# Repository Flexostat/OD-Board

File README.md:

# OD-Board
This repository contains the optical density measurement PCB and firmware source
 and production files for the Flexostat and syphonstat.

### Production_files/PCB/
These are the files that get zipped and sent to the PCB fabricator.

### Production_files/firmware.hex
This is the firmware file to be loaded onto the OD board.  

### seeed_bom.csv
This is the BOM file used by Seeedstudio to assemble the PCB.  If assembled by
Seeedstudio, the light sensors still need to be added afterwards since seeed
does not stock them.

<br />This work is licensed under a <a rel="license" href="http://creativecommons.org/licenses/by/4.0/">Creative Commons Attribution 4.0 International License</a>.

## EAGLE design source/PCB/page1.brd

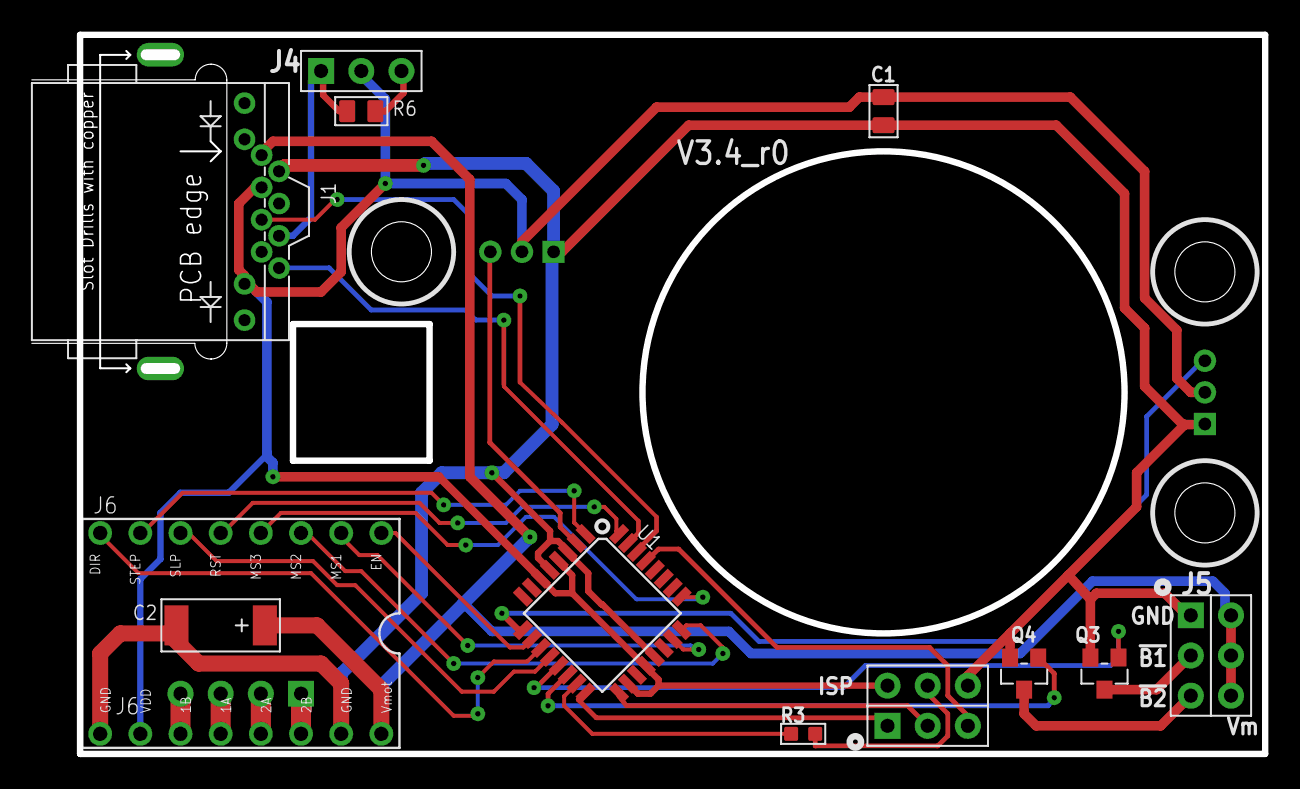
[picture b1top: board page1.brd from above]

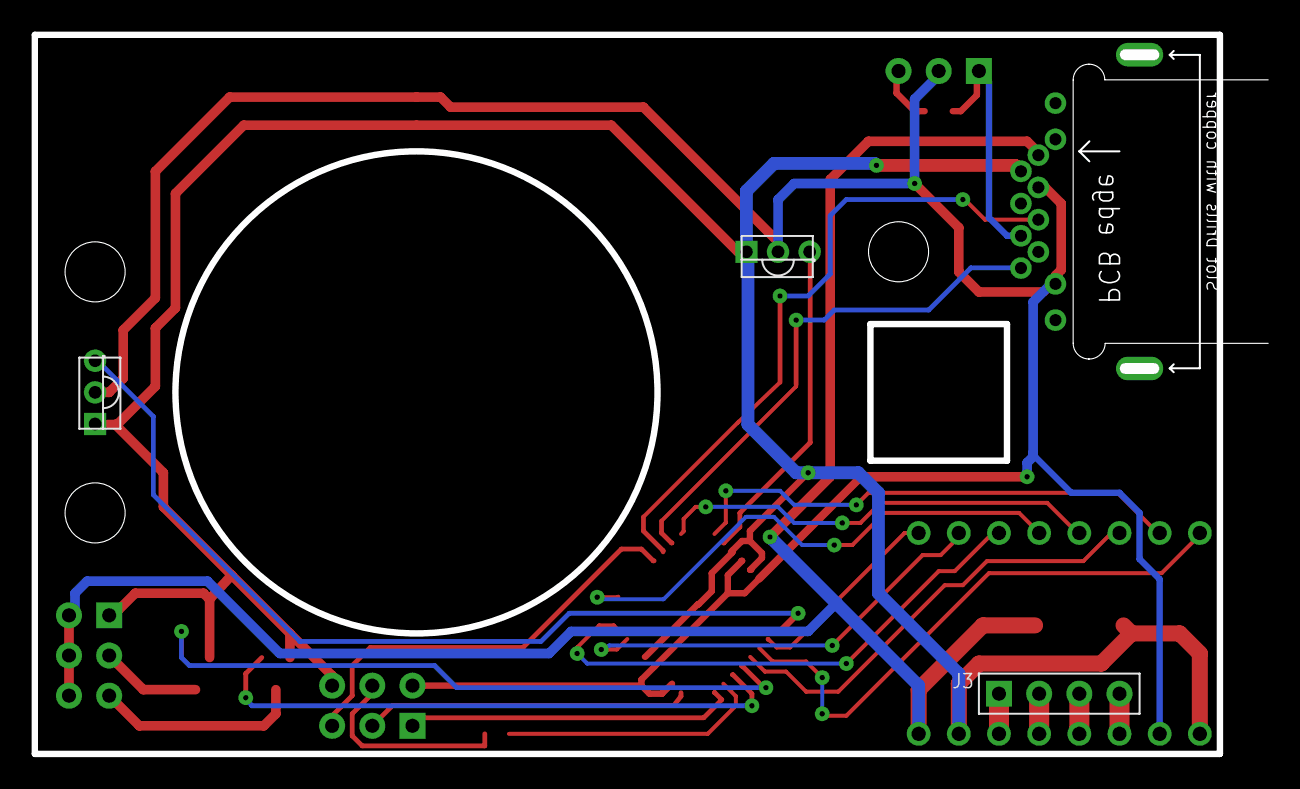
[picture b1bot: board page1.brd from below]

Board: 4 copper layers, 77.5 x 45.2 mm, 15 parts (3 on the bottom side), 30 nets.

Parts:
C1: 1uF; C0805
C2: 47uf; AVX-C
ISP: CONNECTOR-HEADER-2X3P-3460180P1; 2X3P-2.54-2.54-11.6-3.0-BLACK-MALE
J1: MJ88-BX11-RVSL2; RJ45-12+2P-16.3X15.4X11.5MM-IN
J3: 4p-2.54; H4-2.54
J4: CONNECTOR-HEADER-3P-3460810P1; 1X3P-2.54-2.54-11.6-3.0-BLACK-MALE
J5: CONNECTOR-HEADER-2X3P-3460180P1; 2X3P-2.54-2.54-11.6-3.0-BLACK-MALE
Q3, Q4: MOSFET-N-044020001; SOT23
R3: 10k; R0603
R6: 270R; R0805
U1: ATMEGA328P-AU-1030060P1; TQFP32
U$1: A4988BREAKOUT
U$5, U$6: TSL235; TSL235R-2MM-S

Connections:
+5V: C1.2, ISP.6, J1.6, J1.10, J4.2, U1.4, U1.6, U1.18, U1.20, U$1.VDD, U$5.P$2, U$6.P$2
+12V: C2.+, J1.8, J5.4, J5.5, J5.6, U$1.VMOT
EEE: C1.1, C2.-, ISP.4, J1.7, J5.1, Q3.2, Q4.2, U1.3, U1.5, U1.21, U$1.GND, U$1.GND@0, U$5.P$1, U$6.P$1
LF1: U1.2, U$5.P$3
LF2: U1.9, U$6.P$3
M!EN: U1.10, U$1.EN
M!RST: U1.32, U$1.RST
M!SLP: U1.12, U$1.SLP
MDIR: U1.11, U$1.DIR
MISO: ISP.1, U1.16
MOSI: ISP.5, R3.1
MS1: U1.23, U$1.MS1
MS2: U1.24, U$1.MS2
MS3: U1.25, U$1.MS3
unnamed: J1.3, J4.1, R6.1
unnamed: J5.3, Q4.3
unnamed: J5.2, Q3.3
unnamed: J4.3, R6.2
unnamed: J3.1, U$1.2B
unnamed: J3.2, U$1.2A
unnamed: J3.3, U$1.1A
unnamed: J3.4, U$1.1B
OC2A: R3.2, U1.15
OC2B: U1.1, U$1.STEP
PB1: Q3.1, U1.13
PB2: Q4.1, U1.14
RST: ISP.3, U1.29
SCK: ISP.2, U1.17
S_RX: J1.4, U1.30
S_TX: J1.1, U1.31

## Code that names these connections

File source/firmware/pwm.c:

/*
 * pwm.c
 *
 * Created: 8/2/2011 3:10:29 PM
 *  Author: soslab
 */ 
#include "pwm.h"
#include "EEMAP.h"
#include <avr/io.h>
#include <avr/interrupt.h>
#include <avr/eeprom.h>

volatile uint16_t millist;
volatile uint16_t ust;
volatile uint16_t us_p_int;

//setup stir motor PWM
//TODO: convert this to work with timer2
void pwm_init() {
	/******STIR INIT*******/

	DDRD |= 0x08; //PD3:OSC2B output
	DDRD |= 0x04; //PD2 -> !MRST
	DDRD |= 0x40; //PD6 -> !MEN
	DDRD |= 0x80; //PD7 -> MDIR
	DDRB |= 0x01; //PB0 -> !MSLP
	DDRC |= 0x07; //PC0-PC2 output  -> MS1-MS3
	/************************************************************************/
	/*
	MS1 	MS2 	MS3 	Microstep Resolution
	Low 	Low 	Low 	Full step
	High	Low 	Low 	Half step
	Low 	High	Low 	Quarter step
	High	High	Low 	Eighth step
	High	High	High	Sixteenth step                                  */
	/************************************************************************/
	uint8_t stepmode = eeprom_read_byte(EE_ADDR_STEP);
	stepmode = stepmode == 0xff ? 0 : stepmode &0x07;  //take default full steps, mask lower 3 bits
	PORTC &= ~0x07; //PC0-PC2 low = full step
	PORTC |= stepmode;
	//PORTC |= 0x01; //half step
	PORTD |= 0x04; //pull motor reset high
	PORTD &= ~0x40; //pull motor enable low
	PORTB |= 0x01; //pull motor sleep high
	
	
	//CTC mode, toggle on compare match  B
	TCCR2A = 0x02 | 0x10; 
	//cksel /256,
	TCCR2B = 0x06;
	
	//toggle on counter top/2  
	//OCR2A = COUNTER_TOP/2;
	uint8_t ctop = eeprom_read_byte(EE_ADDR_COUNT);
	ctop = (ctop>32 && ctop<=64) ? ctop : COUNTER_TOP;
	OCR2A = ctop;
	us_p_int = (COUNTER_TOP+1)*(256/8);
	OCR2B = 0;
	
	TIMSK2 = 1<<OCIE2A; 
	
}

//one epoch is 2/STIR_SPEED seconds
//takes roughly 120 cycles every US_PER_INT
ISR (TIMER2_COMPA_vect) { 
  ust += us_p_int;
  while (ust>1000) {
	  ust-=1000;
	  millist +=1;
  }
}

uint16_t millis() {
  return millist;
}

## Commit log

2013-03-06 added firmware code
2014-03-18 added eagle files for LED board. version 3.1
2014-03-18 updated to version 3.2 of led PCB
2014-03-19 added BOM file for ordering LED board from seeed studio preassembled
2014-03-19 first test port to new ATMEGA part. should also compile for old 164 part
2014-03-19 added error check at complie time
2014-04-04 added support for LED board version 3.2
2014-04-04 Updated PCB design for ledboard 3.2r1
2014-05-13 reorg directory structure
2014-05-13 more file reorg
2014-05-13 updated c code to reflect new boards. included hex file
2014-08-07 LED board update rev3. Vs and Vss corrected
2014-11-18 fixed whitespace
2014-12-19 millis now counts the full range of uint16_t.
2014-12-19 tabs->spaces. And added PV pulse support on B1
2014-12-19 added syphonstat binary
2014-12-19 now pulls enable pin high for stirring on newest board rev
2015-08-12 added control over stirrer driver OE
2015-08-12 updated bom file for seeed's new format
2015-08-28 fixed bom to align with seeed's new partnumber
2015-09-08 soldering jig
2015-09-30 fixed partnumber changed by seeed
2016-01-23 added back text files
2016-01-23 file structre reorg
2016-01-23 updated PCB
2016-01-23 forgot this in the last push
2016-01-23 fixed file name reference
2016-01-23 updated code to match PCB 3.3
2016-01-23 updated production firmware
2016-02-11 updated footprint for rj45
2016-03-31 updated pcb -- untested!
2017-05-12 updated pcb with better motor drivers -- tested and working.
2017-07-01 updated BOM.
2017-07-01 Fixed two bugs that canceled each other out, as well as removed some dead code.
2017-07-01 more cleanup and added to .gitignore
2017-07-01 added adjustable RPM
2017-08-14 new firmware for speed control
2017-08-22 ignore build dirs
2017-08-22 Redesign from scratch. in KiCAD new design should be easier to assemble and leaves room for better laser alignment
2017-09-01 BOM had M instead of F pin headers for stepper driver
2019-08-23 added kicad temp files
2019-08-23 update to kicad 5
2020-03-09 changed license to CC-BY
2020-03-09 changed to CC-BY
